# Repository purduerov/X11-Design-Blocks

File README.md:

# X11-Design-Blocks

To create a new part:
1. Before you begin work, pull recent updates from the repo with:
	
	`git checkout master`
  
	`git pull`

2. Create a new branch for your part with (replace NEW_BRANCH_NAME with your own _new_ branch name):

	`git checkout -b NEW_BRANCH_NAME`

3. Make your changes in eagle to create the part

4. Add you changes with:

	`git add .`

5. Commit your changes (this saves them) with (replace Your message with an explanation of what was added):

	`git commit -m "YOUR MESSAGE"`

6. Push your changes to the remote repo with (use the same name as before):

	`git push -u origin NEW_BRANCH_NAME`

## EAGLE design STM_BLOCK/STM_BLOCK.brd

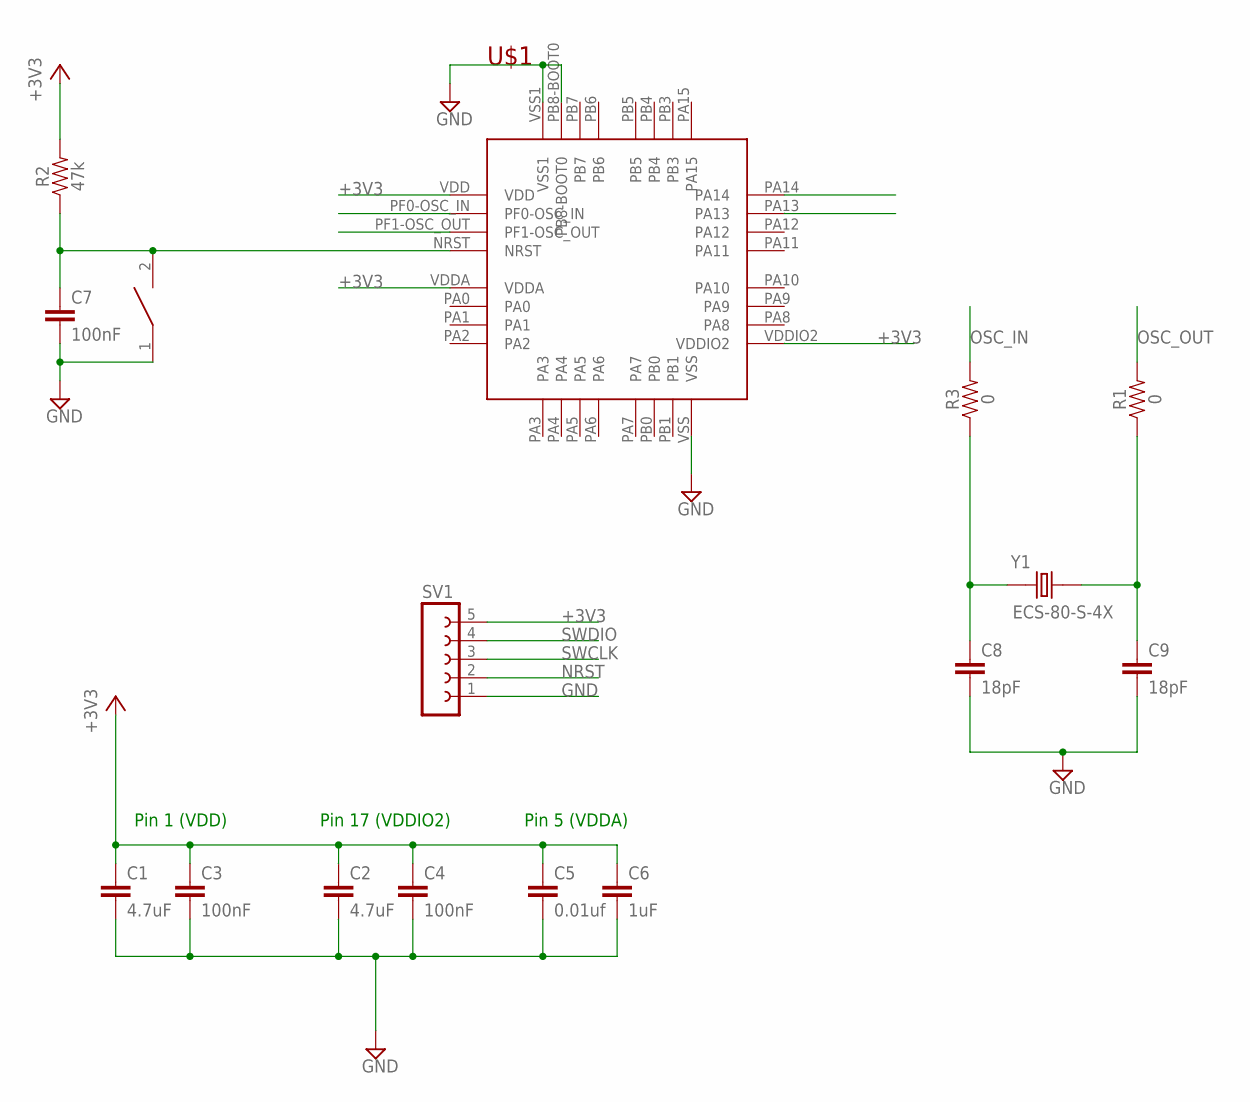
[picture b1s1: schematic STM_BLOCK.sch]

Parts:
C1, C2: 4.7uF; 0603
C3, C4, C7: 100nF; 0603
C5: 0.01uf; 0603
C6: 1uF; 0603
C8, C9: 18pF; 0603
R1, R3: 0; 0603
R2: 47k; 0603
RESET: SWITCH; SW_2512
SV1: FE05-1
U$1: STM32F042K6T6
Y1: ECS-80-S-4X; XTAL_ECS-80-S-4X

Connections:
+3V3: C1.1, C2.1, C3.1, C4.1, C5.1, C6.1, R2.2, SV1.5, U$1.VDD, U$1.VDDA, U$1.VDDIO2
GND: C1.2, C2.2, C3.2, C4.2, C5.2, C6.2, C7.2, C8.2, C9.2, RESET.1, SV1.1, U$1.PB8-BOOT0, U$1.VSS, U$1.VSS1
unnamed: C9.1, R1.1, Y1.2
unnamed: C8.1, R3.1, Y1.1
NRST: C7.1, R2.1, RESET.2, SV1.2, U$1.NRST
OSC_IN: R3.2, U$1.PF0-OSC_IN
OSC_OUT: R1.2, U$1.PF1-OSC_OUT
SWCLK: SV1.3, U$1.PA14
SWDIO: SV1.4, U$1.PA13

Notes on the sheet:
Pin 1 (VDD)
Pin 17 (VDDIO2)
Pin 5 (VDDA)

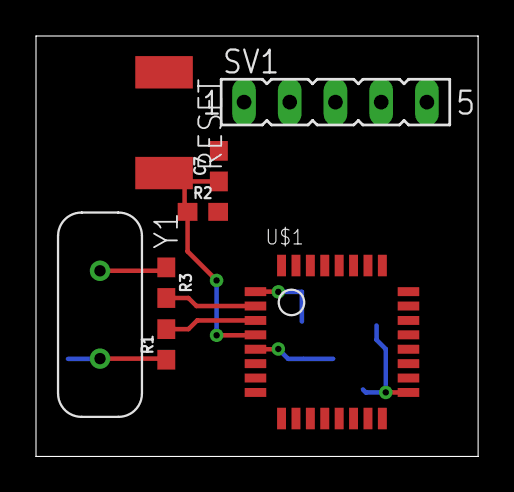
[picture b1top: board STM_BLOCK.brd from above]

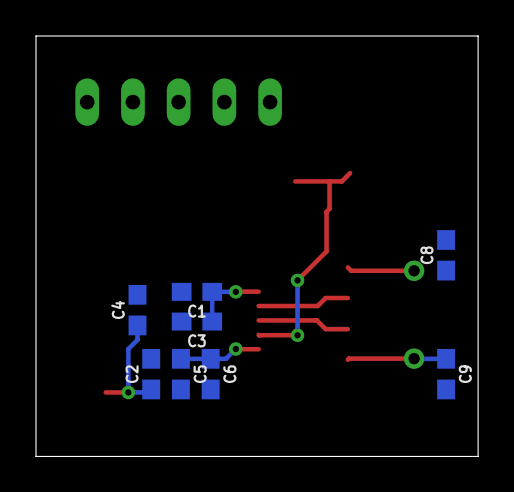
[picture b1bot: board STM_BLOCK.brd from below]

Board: 2 copper layers, 24.6 x 23.4 mm, 16 parts (8 on the bottom side), 9 nets.

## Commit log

2018-10-16 Added readme
2018-10-16 STM32F042 Block
    Added block for STM
2018-10-16 Added IMU design block
2018-10-16 Fixed STM Design Block

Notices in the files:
parts and their libraries:
SparkFun-Capacitors: Licensing: Creative Commons ShareAlike 4.0 International - https://creativecommons.org/licenses/by-sa/4.0
